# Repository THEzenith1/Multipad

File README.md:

# Multipad v1

A modular solution to make your workflow faster. Designed spesifically for video and code editing. 

## How it Works

Modules (M1,etc) slot into the two slots of the Hub (H2) magnetically and automatically connect to the attached computer. The modules are 100% hot swap. Extra expandability can be achived by attaching Stands (S1) to the bottom of the H2. These act as a host for the H2 and modules on it. (meaning when using the stand module plug your computer into the stand instead of the hub)

## Features 

- QMK/VIA Compatability (M1,M1_RGB)

- Deej Compatability (https://github.com/omriharel/deej)

- Windows + MacOS Compatability (except M2) 
- Up to 2 Hot Swappable modules on H2
- Easy to expand usb interface in the 4 pin module interface
- Magnetic stands (S1) to expand multipad capability

## Current Modules

✅M1_RGB- A 12 key macropad with ARGB lights on keys 5-12 and VIA support (this is sometimes refured to in the docs as M3)

✅M2- 4 Volume sliders running the deej firmwere

✅M4- A scrol wheel with 4 keys for davinchi resolve (Not VIA compatable. Key configuration in the aurduino file)

✅M5- Coster

✅S1- Attaches to the back of H2 to add 3 USB-C ports 

🚧S2- Adds a battery and wireless capabilities to the entire Multipad system

🚧M6- Spotify song viewer and media control with a screen

❌M1- An 11 key macropad with VIA support (depreciated module with 1st gen pcb)

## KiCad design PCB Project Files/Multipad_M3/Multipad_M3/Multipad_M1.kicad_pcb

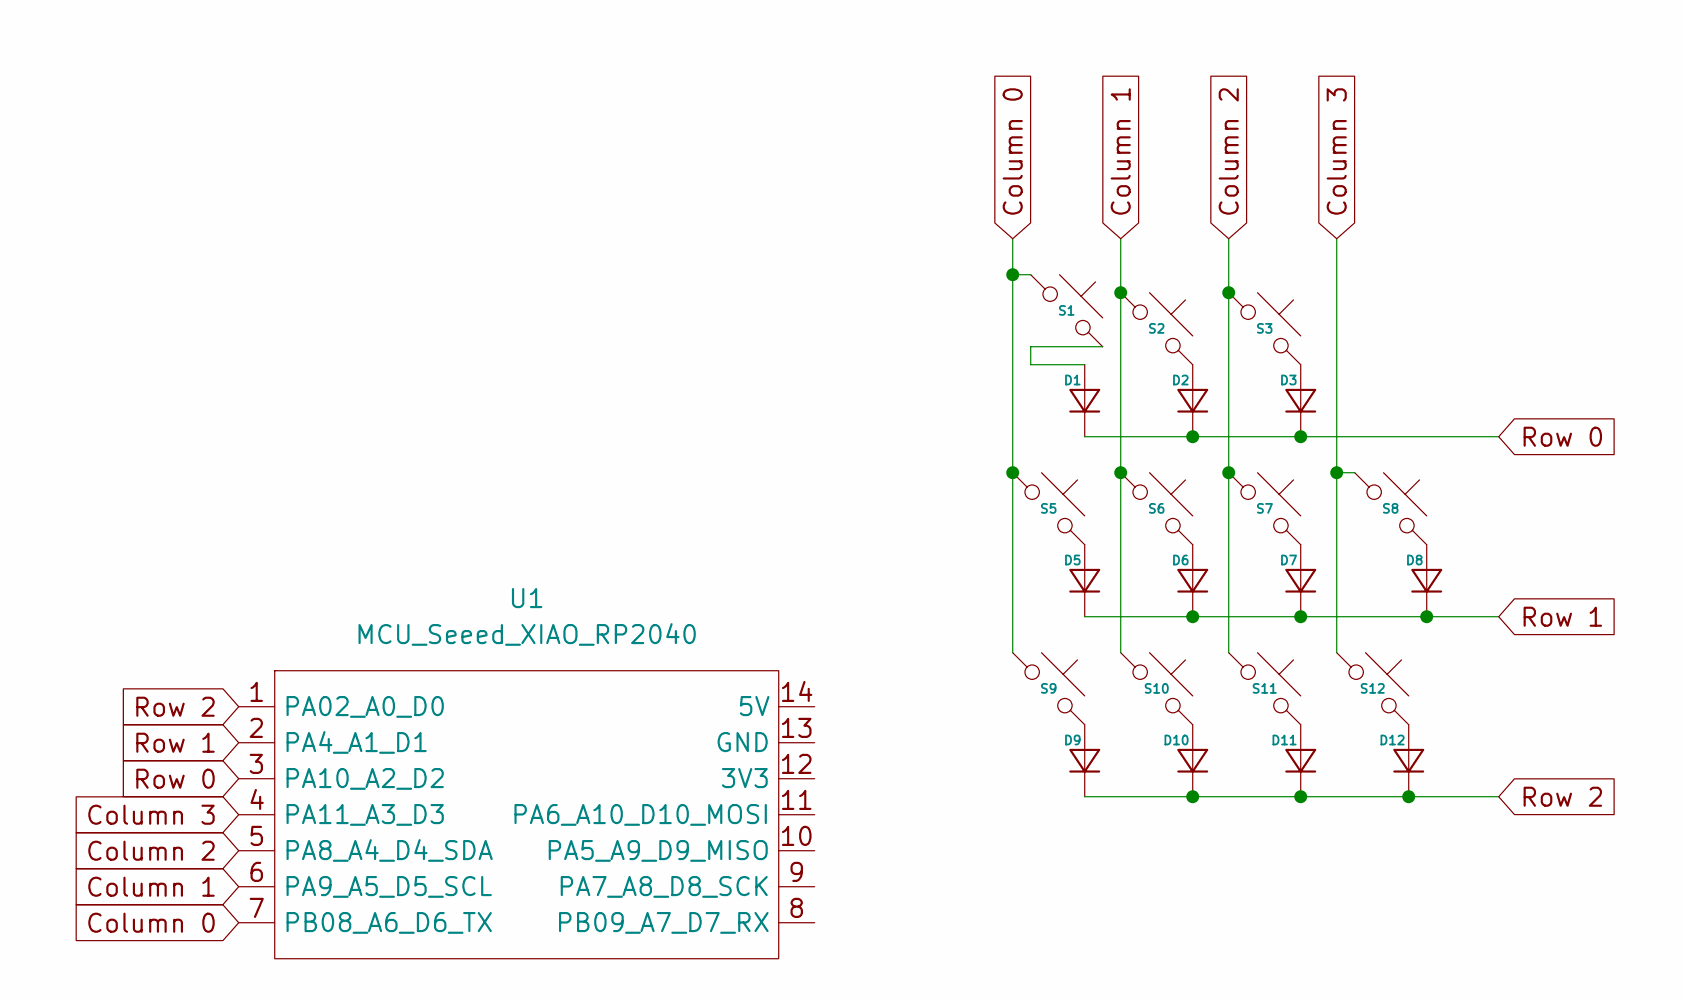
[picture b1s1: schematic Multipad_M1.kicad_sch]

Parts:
D1, D2, D3, D5, D6, D7, D8, D9, D10, D11, D12: Diode_DO-35
S1, S2, S3, S5, S6, S7, S8, S9, S10, S11, S12: Choc_V1V2_1.00u
U1: MCU_Seeed_XIAO_RP2040; Seeed_XIAO_RP2040

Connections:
Column 0: S1.1, S5.1, S9.1, U1.7 (PB08_A6_D6_TX)
Column 1: S2.1, S6.1, S10.1, U1.6 (PA9_A5_D5_SCL)
Column 2: S3.1, S7.1, S11.1, U1.5 (PA8_A4_D4_SDA)
Column 3: S8.1, S12.1, U1.4 (PA11_A3_D3)
unnamed: D1.2 (A), S1.2
unnamed: D2.2 (A), S2.2
unnamed: D3.2 (A), S3.2
unnamed: D5.2 (A), S5.2
unnamed: D6.2 (A), S6.2
unnamed: D7.2 (A), S7.2
unnamed: D8.2 (A), S8.2
unnamed: D9.2 (A), S9.2
unnamed: D10.2 (A), S10.2
unnamed: D11.2 (A), S11.2
unnamed: D12.2 (A), S12.2
Row 0: D1.1 (K), D2.1 (K), D3.1 (K), U1.3 (PA10_A2_D2)
Row 1: D5.1 (K), D6.1 (K), D7.1 (K), D8.1 (K), U1.2 (PA4_A1_D1)
Row 2: D9.1 (K), D10.1 (K), D11.1 (K), D12.1 (K), U1.1 (PA02_A0_D0)

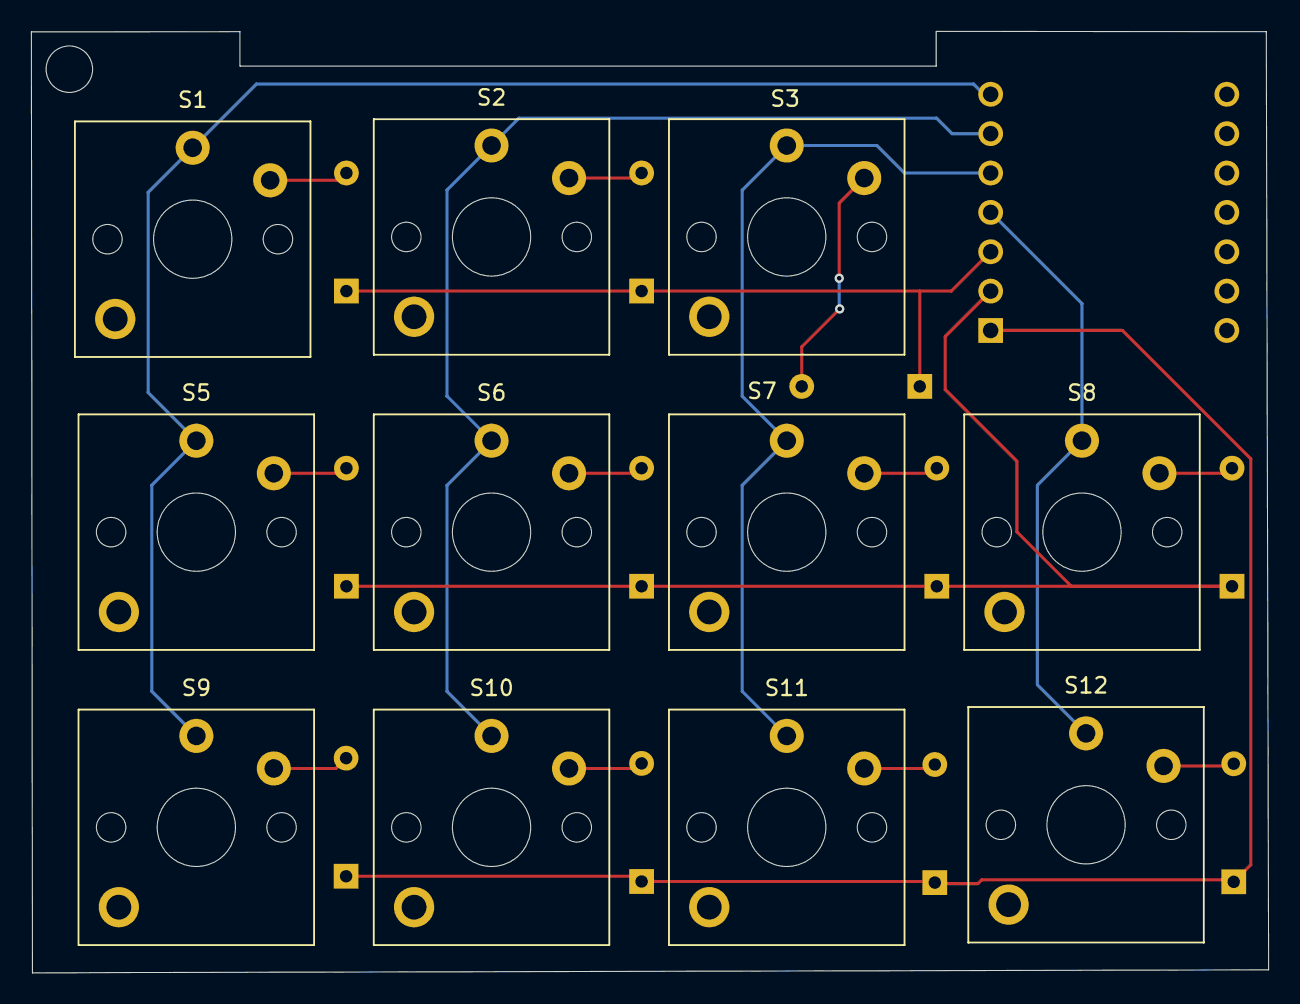
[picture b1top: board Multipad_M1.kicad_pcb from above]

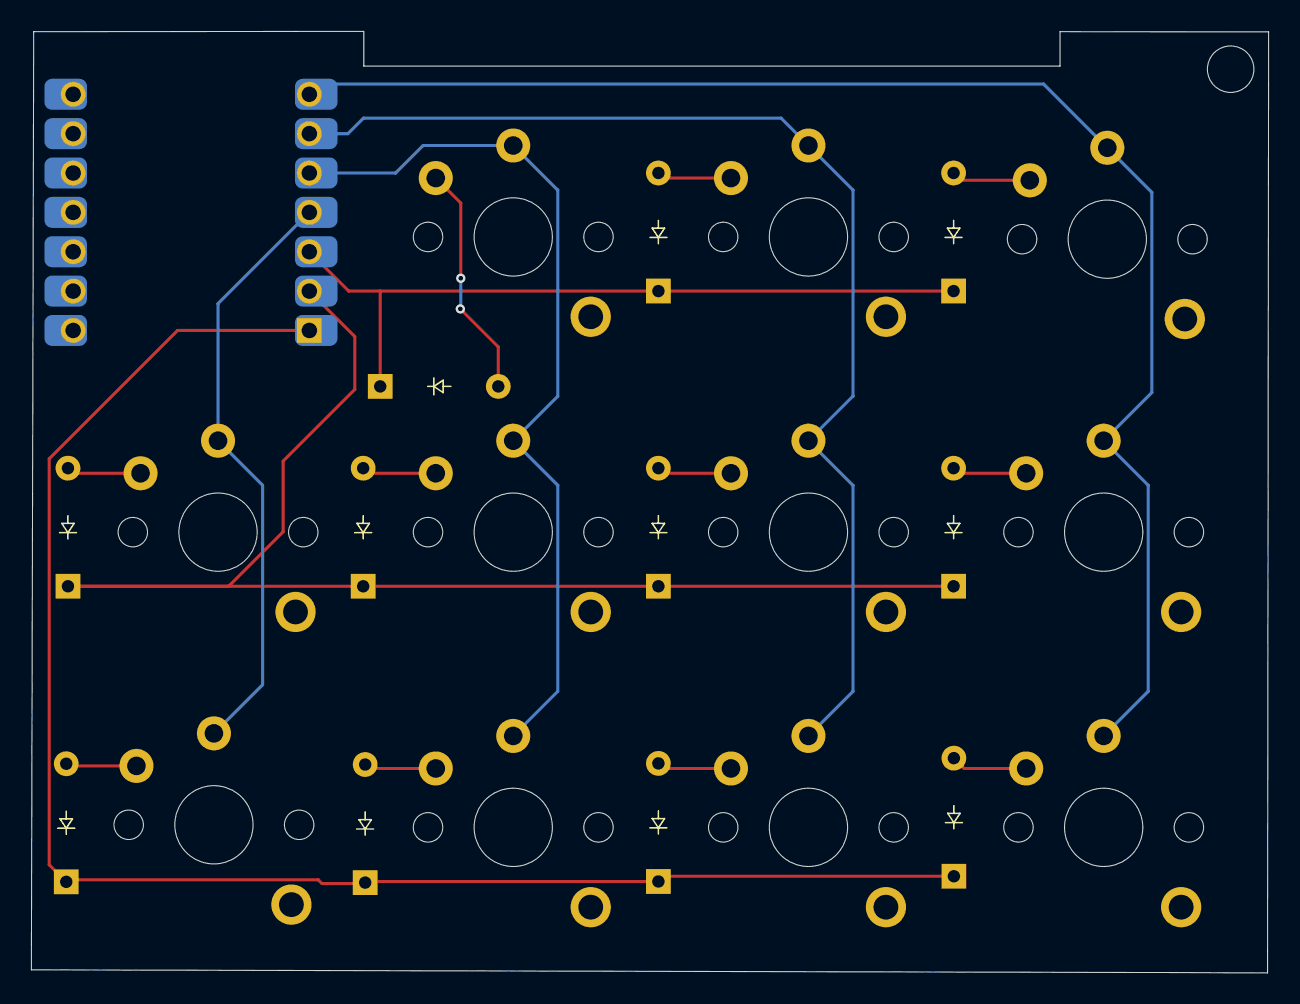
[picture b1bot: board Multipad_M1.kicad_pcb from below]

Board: 2 copper layers, 79.8 x 60.8 mm, 23 parts (12 on the bottom side), 18 nets.

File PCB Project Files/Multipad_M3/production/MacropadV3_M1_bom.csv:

Designator,Footprint,Quantity,Value,LCSC Part #
"D1, D10, D11, D12, D2, D3, D4, D5, D6, D7, D8, D9",Diode_DO-35,12,~,
"S1, S10, S11, S12, S2, S3, S4, S5, S6, S7, S8, S9",MX_PCB_1.00u,12,~,
U2,Adafruit_QTPY_2040,1,~,

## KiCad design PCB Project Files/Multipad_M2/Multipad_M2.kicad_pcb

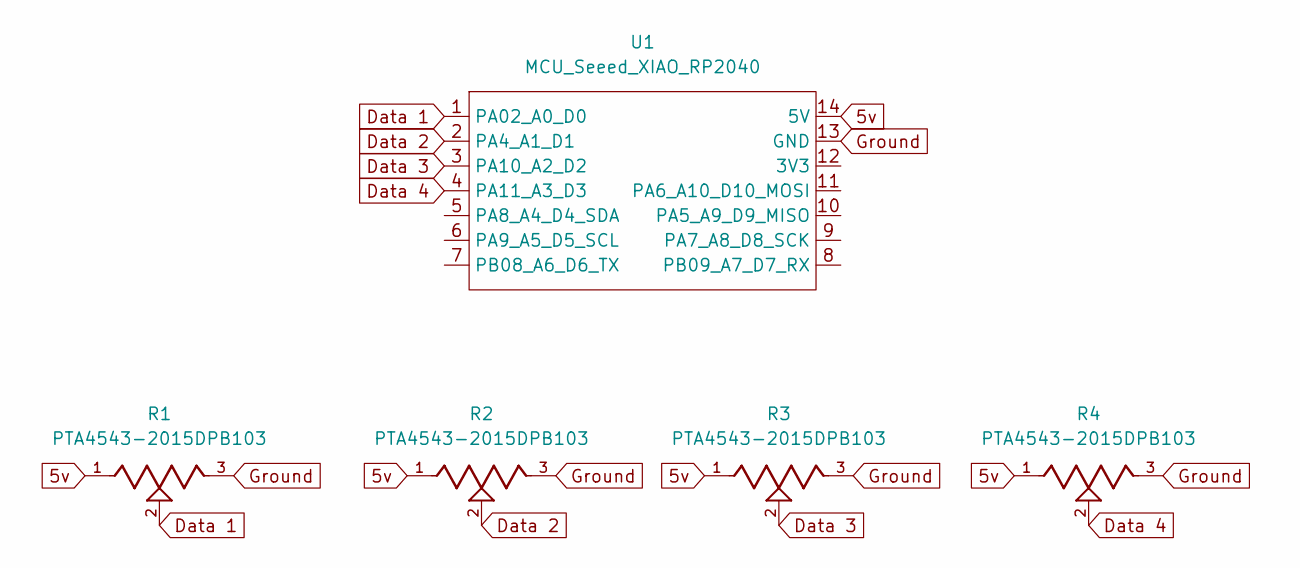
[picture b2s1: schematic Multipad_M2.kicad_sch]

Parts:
R1, R2, R3, R4: PTA4543-2015DPB103; TRIM_PTA4543-2015DPB103; PARTREV 04/21
U1: MCU_Seeed_XIAO_RP2040; Seeed_XIAO_RP2040

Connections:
5v: R1.1, R2.1, R3.1, R4.1, U1.14 (5V)
Data 1: R1.2, U1.1 (PA02_A0_D0)
Data 2: R2.2, U1.2 (PA4_A1_D1)
Data 3: R3.2, U1.3 (PA10_A2_D2)
Data 4: R4.2, U1.4 (PA11_A3_D3)
Ground: R1.3, R2.3, R3.3, R4.3, U1.13 (GND)

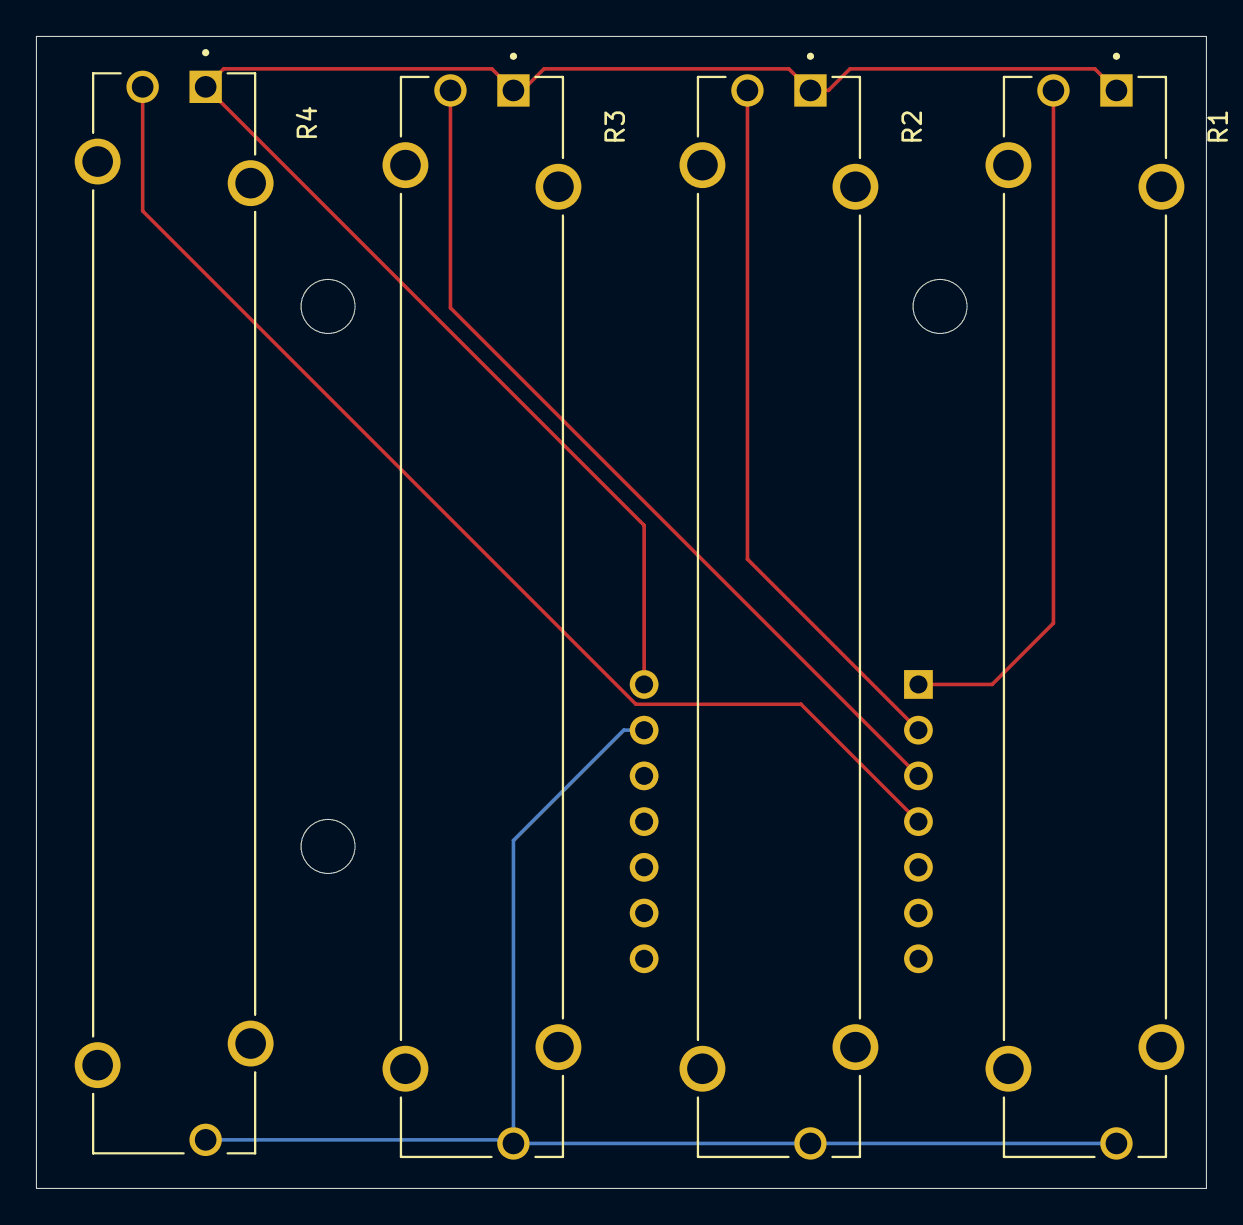
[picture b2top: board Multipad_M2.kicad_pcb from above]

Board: 2 copper layers, 65.0 x 64.0 mm, 5 parts (1 on the bottom side), 6 nets.

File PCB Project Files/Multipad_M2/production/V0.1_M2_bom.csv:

Designator,Footprint,Quantity,Value,LCSC Part #
"R1, R2, R3, R4",TRIM_PTA4543-2015DPB103,4,PTA4543-2015DPB103,
U1,Seeed_XIAO_RP2040,1,MCU_Seeed_XIAO_RP2040,
